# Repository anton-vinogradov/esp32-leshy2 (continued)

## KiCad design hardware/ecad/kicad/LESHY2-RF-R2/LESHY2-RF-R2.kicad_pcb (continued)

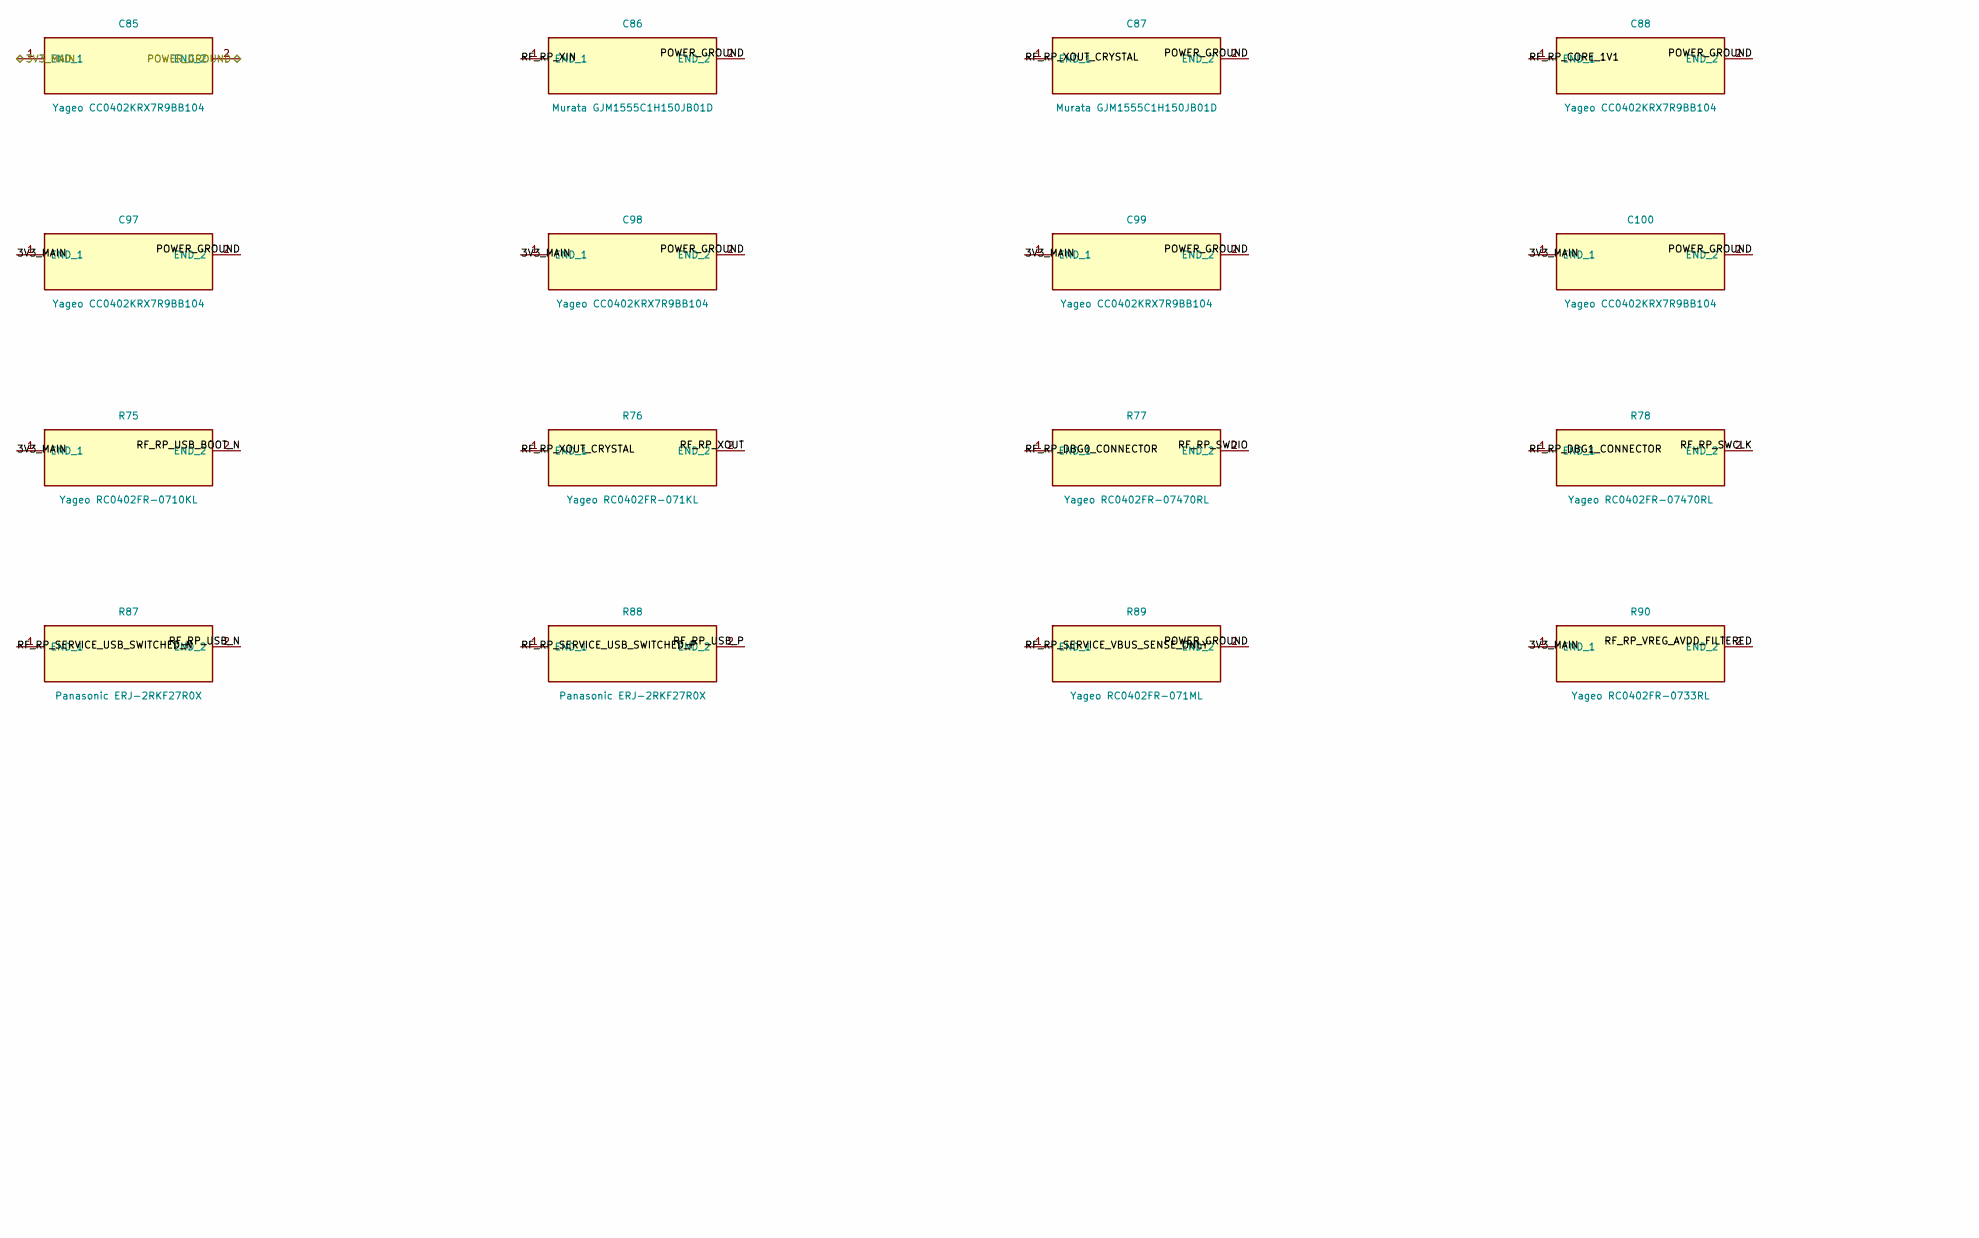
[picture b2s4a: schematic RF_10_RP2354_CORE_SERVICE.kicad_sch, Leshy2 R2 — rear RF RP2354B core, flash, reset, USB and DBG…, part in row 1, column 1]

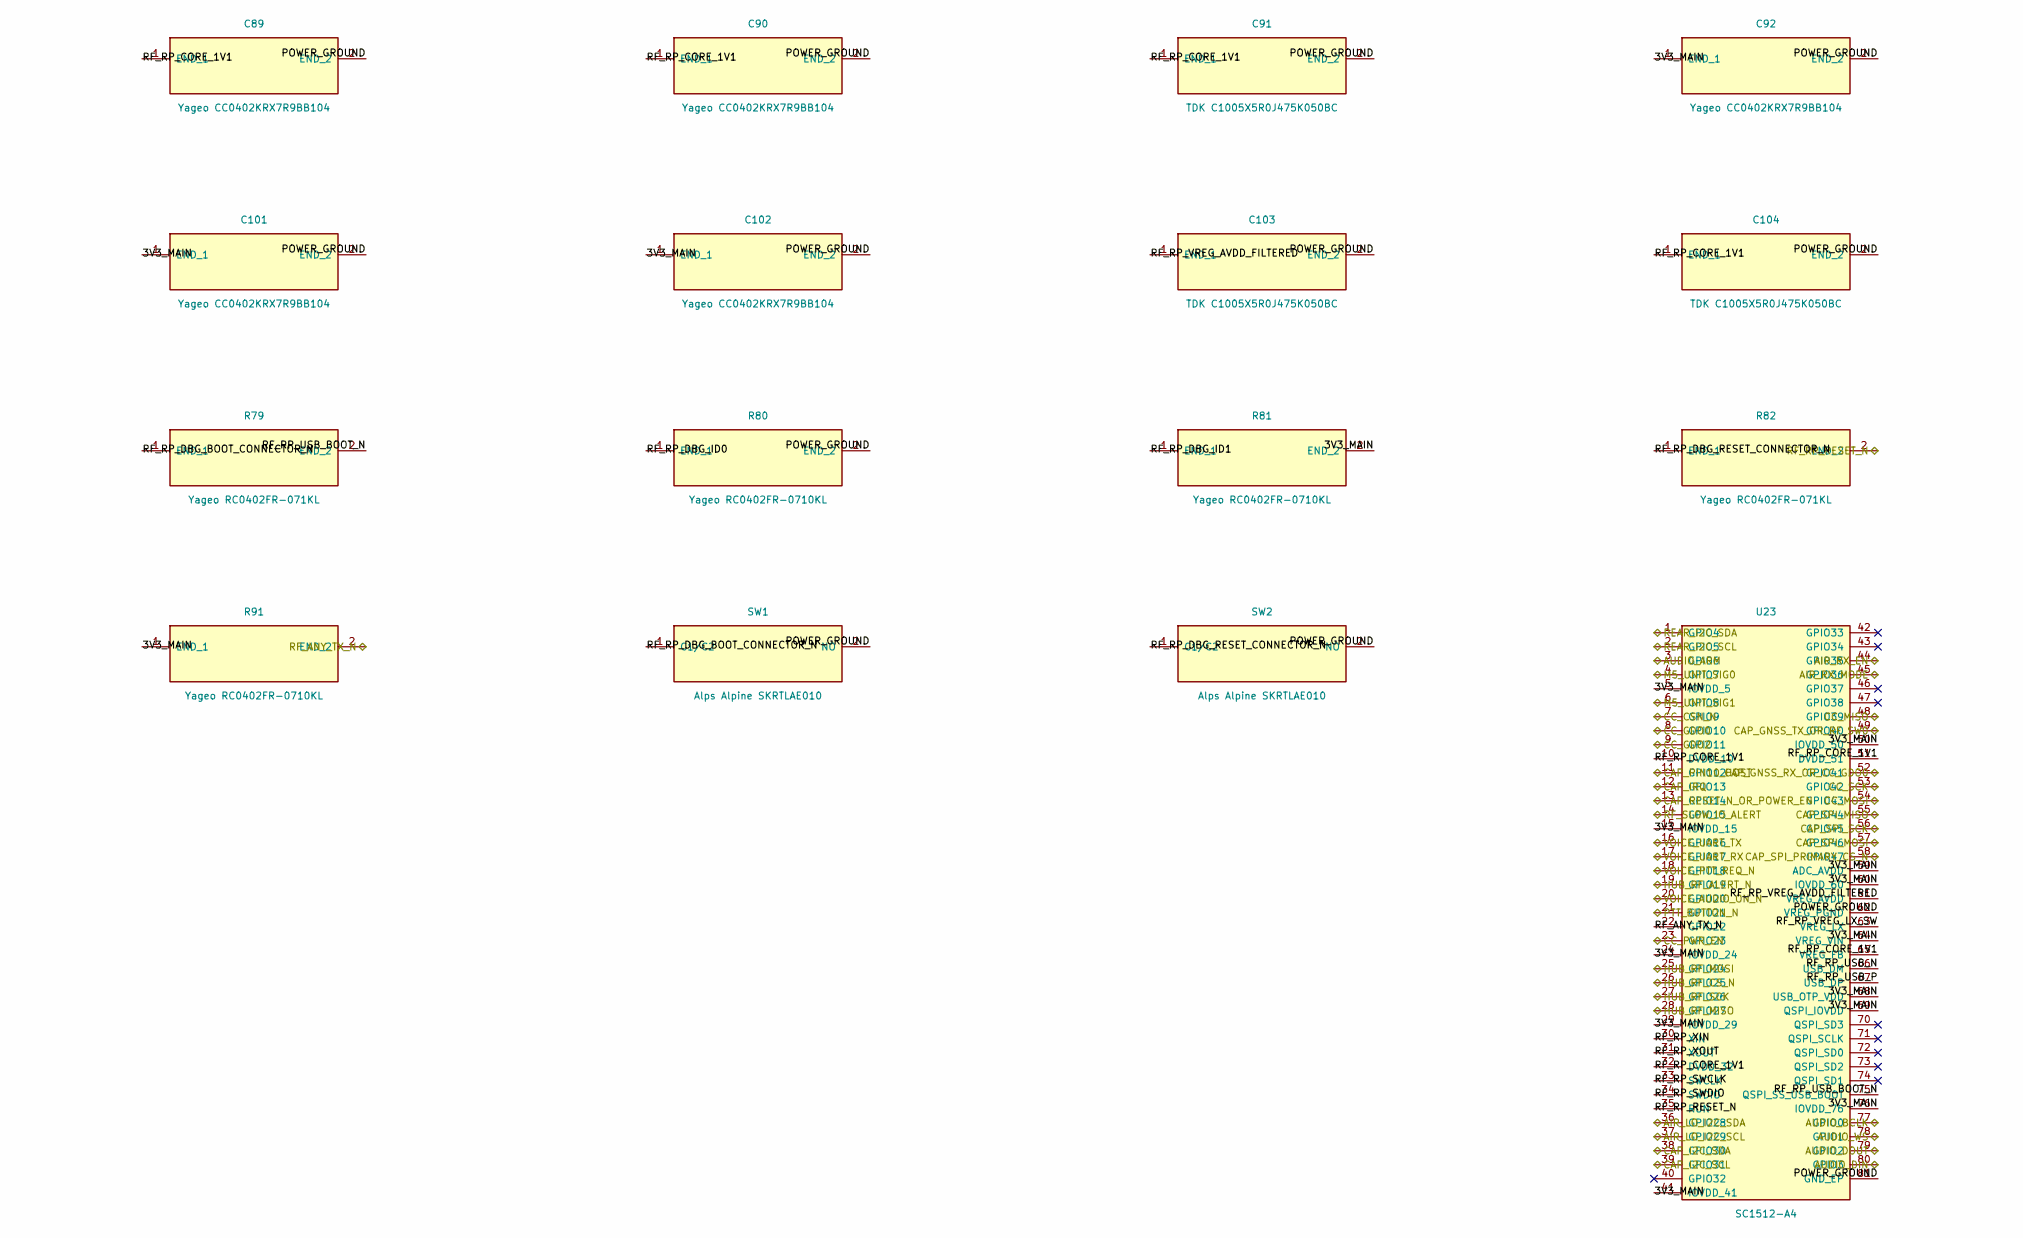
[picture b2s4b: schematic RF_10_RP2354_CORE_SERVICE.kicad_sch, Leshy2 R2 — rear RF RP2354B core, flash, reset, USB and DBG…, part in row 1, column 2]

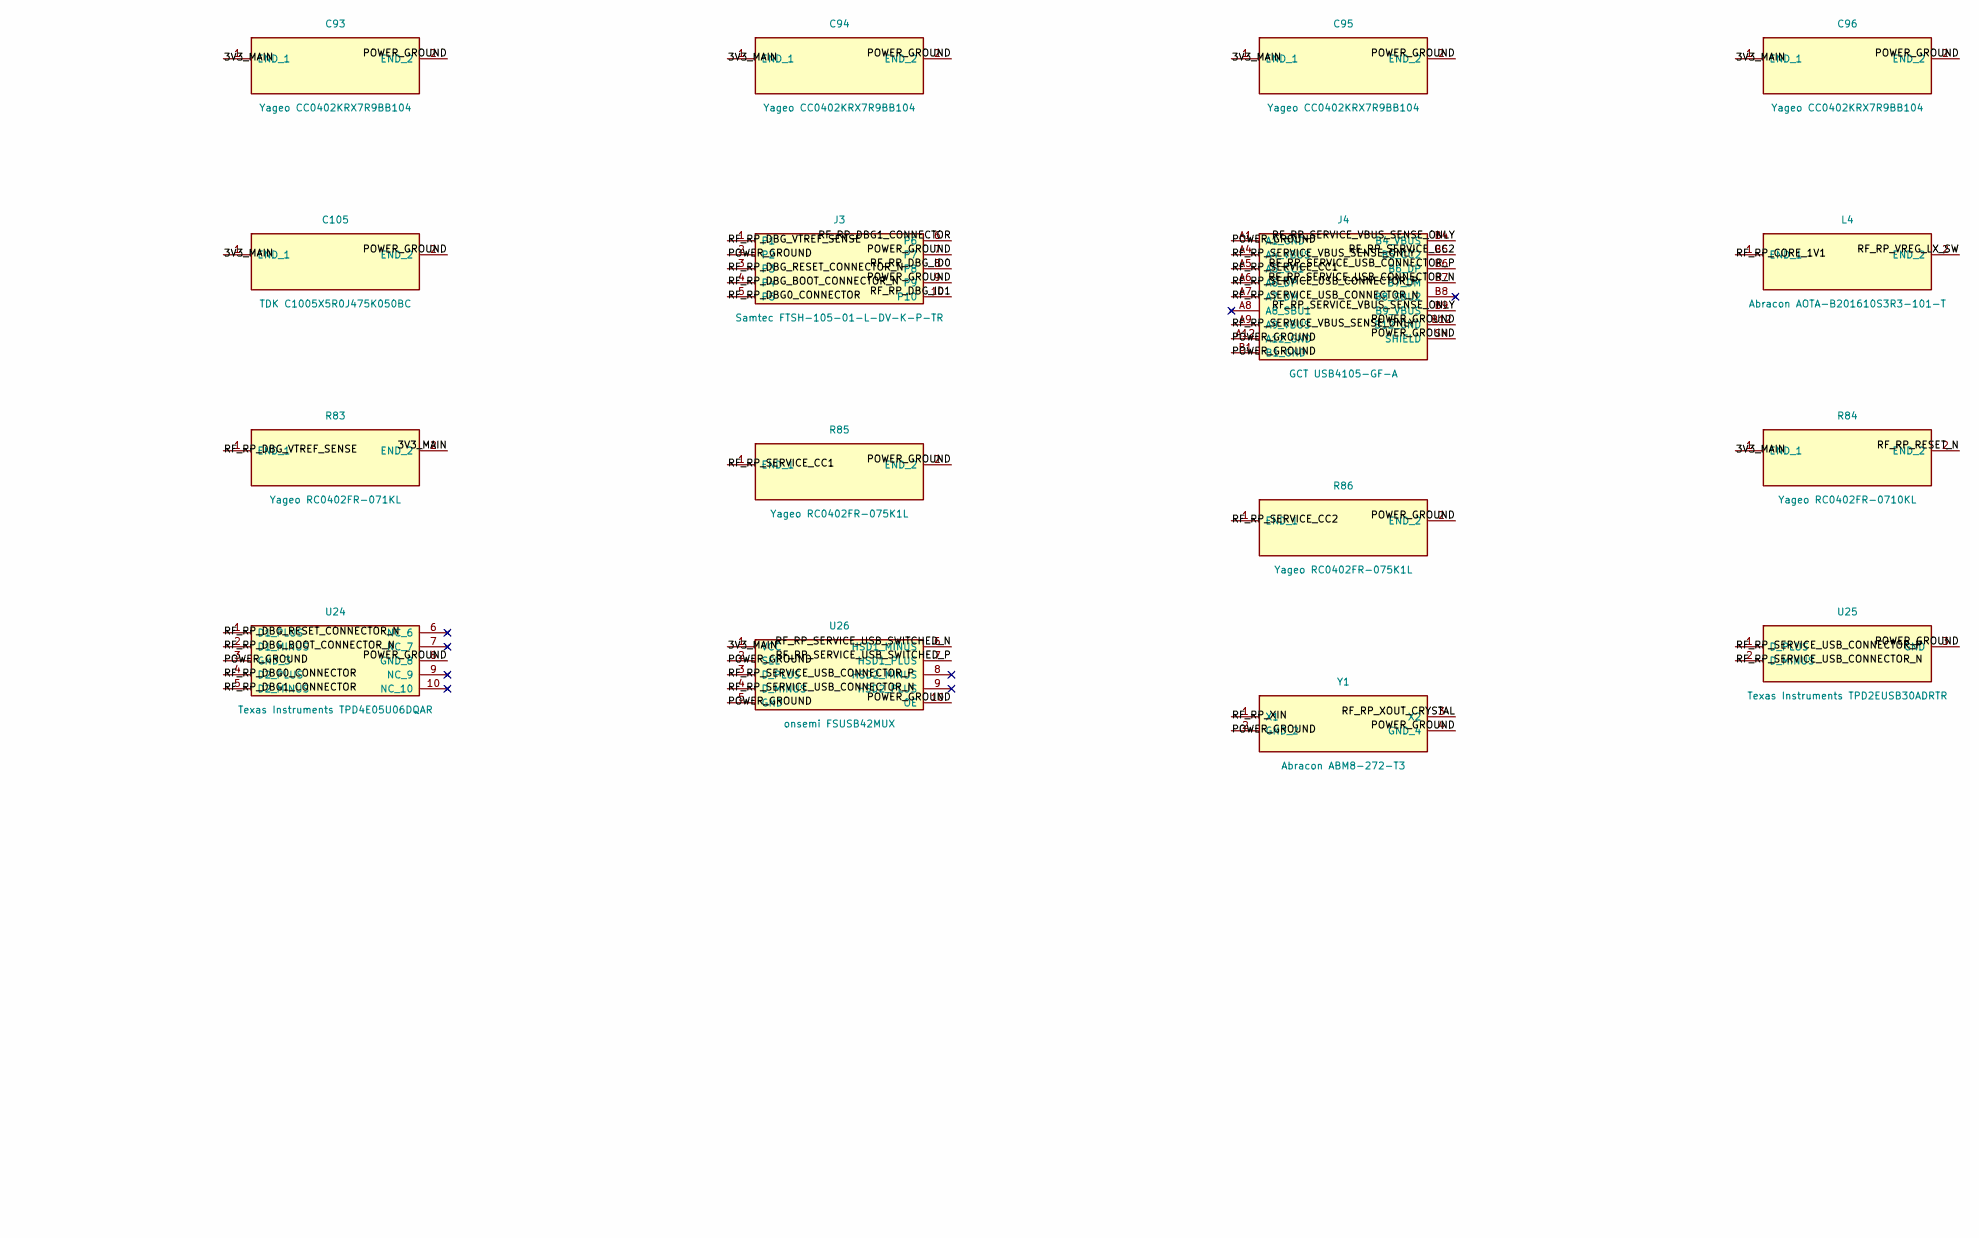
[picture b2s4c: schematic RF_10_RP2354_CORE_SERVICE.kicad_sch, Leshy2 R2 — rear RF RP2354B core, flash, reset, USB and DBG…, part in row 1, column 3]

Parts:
C85, C88, C89, C90, C92, C93, C94, C95, C96, C97, C98, C99, C100, C101, C102: Yageo CC0402KRX7R9BB104; C_0402_1005Metric
C86, C87: Murata GJM1555C1H150JB01D; C_0402_1005Metric
C91, C103, C104, C105: TDK C1005X5R0J475K050BC; C_0402_1005Metric
J3: Samtec FTSH-105-01-L-DV-K-P-TR; FTSH-105-01-L-DV-K-P-TR
J4: GCT USB4105-GF-A; USB_C_Receptacle_GCT_USB4105-xx-A_16P_TopMnt_Horizontal
L4: Abracon AOTA-B201610S3R3-101-T; L_Murata_DFE201610P
R75, R80, R81, R84, R91: Yageo RC0402FR-0710KL; R_0402_1005Metric
R76, R79, R82, R83: Yageo RC0402FR-071KL; R_0402_1005Metric
R77, R78: Yageo RC0402FR-07470RL; R_0402_1005Metric
R85, R86: Yageo RC0402FR-075K1L; R_0402_1005Metric
R87, R88: Panasonic ERJ-2RKF27R0X; R_0402_1005Metric
R89: Yageo RC0402FR-071ML; R_0402_1005Metric
R90: Yageo RC0402FR-0733RL; R_0402_1005Metric
SW1, SW2: Alps Alpine SKRTLAE010; SW_Push_1P1T-MP_NO_Horizontal_Alps_SKRTLAE010
U23: SC1512-A4; QFN-80-1EP_10x10mm_P0.4mm_EP3.4x3.4mm
U24: Texas Instruments TPD4E05U06DQAR; USON-10_2.5x1.0mm_P0.5mm
U25: Texas Instruments TPD2EUSB30ADRTR; Texas_DRT-3
U26: onsemi FSUSB42MUX; MSOP-10_3x3mm_P0.5mm
Y1: Abracon ABM8-272-T3; Crystal_SMD_Abracon_ABM8G-4Pin_3.2x2.5mm

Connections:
/RF_01_USB_PD_CHARGE/POWER_GROUND: C85.2 (END_2), C86.2 (END_2), C87.2 (END_2), C88.2 (END_2), C89.2 (END_2), C90.2 (END_2), C91.2 (END_2), C92.2 (END_2), C93.2 (END_2), C94.2 (END_2), C95.2 (END_2), C96.2 (END_2), C97.2 (END_2), C98.2 (END_2), C99.2 (END_2), C100.2 (END_2), C101.2 (END_2), C102.2 (END_2), C103.2 (END_2), C104.2 (END_2), C105.2 (END_2), J3.2, J3.7, J3.9, J4.A1 (A1_GND), J4.A12 (A12_GND), J4.B1 (B1_GND), J4.B12 (B12_GND), J4.SH (SHIELD), R80.2 (END_2), R85.2 (END_2), R86.2 (END_2), R89.2 (END_2), SW1.2 (NO), SW2.2 (NO), U23.62 (VREG_PGND), U23.81 (GND_EP), U24.3 (GND_3), U24.8 (GND_8), U25.3 (GND), U26.2 (SEL), U26.5 (GND), U26.10 (OE), Y1.2 (GND_2), Y1.4 (GND_4); also elsewhere on the board
/RF_02_PACK_SAFETY_AON/3V3_MAIN: C85.1 (END_1), C92.1 (END_1), C93.1 (END_1), C94.1 (END_1), C95.1 (END_1), C96.1 (END_1), C97.1 (END_1), C98.1 (END_1), C99.1 (END_1), C100.1 (END_1), C101.1 (END_1), C102.1 (END_1), C105.1 (END_1), R75.1 (END_1), R81.2 (END_2), R83.2 (END_2), R84.1 (END_1), R90.1 (END_1), R91.1 (END_1), U23.5 (IOVDD_5), U23.15 (IOVDD_15), U23.24 (IOVDD_24), U23.29 (IOVDD_29), U23.41 (IOVDD_41), U23.50 (IOVDD_50), U23.59 (ADC_AVDD), U23.60 (IOVDD_60), U23.64 (VREG_VIN), U23.68 (USB_OTP_VDD), U23.69 (QSPI_IOVDD), U23.76 (IOVDD_76), U26.1 (VCC); also elsewhere on the board
/RF_10_RP2354_CORE_SERVICE/AUDIO_BCLK: U23.77 (GPIO0); also elsewhere on the board
/RF_10_RP2354_CORE_SERVICE/AUDIO_DIN: U23.80 (GPIO3); also elsewhere on the board
/RF_10_RP2354_CORE_SERVICE/AUDIO_DOUT: U23.79 (GPIO2); also elsewhere on the board
/RF_10_RP2354_CORE_SERVICE/AUDIO_WS: U23.78 (GPIO1); also elsewhere on the board
/RF_10_RP2354_CORE_SERVICE/CAP_GNSS_RX_OR_CC_GDO0: U23.52 (GPIO41); also elsewhere on the board
/RF_10_RP2354_CORE_SERVICE/CAP_GNSS_TX_OR_RF_SW0: U23.49 (GPIO40); also elsewhere on the board
/RF_10_RP2354_CORE_SERVICE/CAP_IRQ: U23.12 (GPIO13); also elsewhere on the board
/RF_10_RP2354_CORE_SERVICE/CAP_PIN10_HOST: U23.11 (GPIO12); also elsewhere on the board
/RF_10_RP2354_CORE_SERVICE/CAP_RESET_N_OR_POWER_EN: U23.13 (GPIO14); also elsewhere on the board
/RF_10_RP2354_CORE_SERVICE/CAP_SPI_MISO: U23.55 (GPIO44); also elsewhere on the board
/RF_10_RP2354_CORE_SERVICE/CAP_SPI_MOSI: U23.57 (GPIO46); also elsewhere on the board
/RF_10_RP2354_CORE_SERVICE/CAP_SPI_PRIMARY_CS_N: U23.58 (GPIO47); also elsewhere on the board
/RF_10_RP2354_CORE_SERVICE/CAP_SPI_SCK: U23.56 (GPIO45); also elsewhere on the board
/RF_10_RP2354_CORE_SERVICE/CC_PWR_EN: U23.23 (GPIO23); also elsewhere on the board
/RF_10_RP2354_CORE_SERVICE/HUB_RF_ALERT_N: U23.19 (GPIO19); also elsewhere on the board
/RF_10_RP2354_CORE_SERVICE/HUB_RF_CS_N: U23.26 (GPIO25); also elsewhere on the board
/RF_10_RP2354_CORE_SERVICE/HUB_RF_MISO: U23.28 (GPIO27); also elsewhere on the board
/RF_10_RP2354_CORE_SERVICE/HUB_RF_MOSI: U23.25 (GPIO24); also elsewhere on the board
/RF_10_RP2354_CORE_SERVICE/HUB_RF_SCK: U23.27 (GPIO26); also elsewhere on the board
/RF_10_RP2354_CORE_SERVICE/M5_UNIT_SIG0: U23.4 (GPIO7); also elsewhere on the board
/RF_10_RP2354_CORE_SERVICE/M5_UNIT_SIG1: U23.6 (GPIO8); also elsewhere on the board
/RF_10_RP2354_CORE_SERVICE/PTT_BUTTON_N: U23.21 (GPIO21); also elsewhere on the board
/RF_10_RP2354_CORE_SERVICE/RF_ANY_TX_N: R91.2 (END_2), U23.22 (GPIO22); also elsewhere on the board
/RF_10_RP2354_CORE_SERVICE/RF_RP_CORE_1V1: C88.1 (END_1), C89.1 (END_1), C90.1 (END_1), C91.1 (END_1), C104.1 (END_1), L4.1 (END_1), U23.10 (DVDD_10), U23.32 (DVDD_32), U23.51 (DVDD_51), U23.65 (VREG_FB)
/RF_10_RP2354_CORE_SERVICE/RF_RP_DBG0_CONNECTOR: J3.5, R77.1 (END_1), U24.4 (D2_PLUS)
/RF_10_RP2354_CORE_SERVICE/RF_RP_DBG1_CONNECTOR: J3.6, R78.1 (END_1), U24.5 (D2_MINUS)
/RF_10_RP2354_CORE_SERVICE/RF_RP_DBG_BOOT_CONNECTOR_N: J3.4, R79.1 (END_1), SW1.1 (C1/C2), U24.2 (D1_MINUS)
/RF_10_RP2354_CORE_SERVICE/RF_RP_DBG_ID0: J3.8, R80.1 (END_1)
/RF_10_RP2354_CORE_SERVICE/RF_RP_DBG_ID1: J3.10, R81.1 (END_1)
/RF_10_RP2354_CORE_SERVICE/RF_RP_DBG_RESET_CONNECTOR_N: J3.3, R82.1 (END_1), SW2.1 (C1/C2), U24.1 (D1_PLUS)
/RF_10_RP2354_CORE_SERVICE/RF_RP_DBG_VTREF_SENSE: J3.1, R83.1 (END_1)
/RF_10_RP2354_CORE_SERVICE/RF_RP_RESET_N: R82.2 (END_2), R84.2 (END_2), U23.35 (RUN); also elsewhere on the board
/RF_10_RP2354_CORE_SERVICE/RF_RP_SERVICE_CC1: J4.A5 (A5_CC1), R85.1 (END_1)
/RF_10_RP2354_CORE_SERVICE/RF_RP_SERVICE_CC2: J4.B5 (B5_CC2), R86.1 (END_1)
/RF_10_RP2354_CORE_SERVICE/RF_RP_SERVICE_USB_CONNECTOR_N: J4.A7 (A7_DM), J4.B7 (B7_DM), U25.2 (D_MINUS), U26.4 (D_MINUS)
/RF_10_RP2354_CORE_SERVICE/RF_RP_SERVICE_USB_CONNECTOR_P: J4.A6 (A6_DP), J4.B6 (B6_DP), U25.1 (D_PLUS), U26.3 (D_PLUS)
/RF_10_RP2354_CORE_SERVICE/RF_RP_SERVICE_USB_SWITCHED_N: R87.1 (END_1), U26.6 (HSD1_MINUS)
/RF_10_RP2354_CORE_SERVICE/RF_RP_SERVICE_USB_SWITCHED_P: R88.1 (END_1), U26.7 (HSD1_PLUS)
/RF_10_RP2354_CORE_SERVICE/RF_RP_SERVICE_VBUS_SENSE_ONLY: J4.A4 (A4_VBUS), J4.A9 (A9_VBUS), J4.B4 (B4_VBUS), J4.B9 (B9_VBUS), R89.1 (END_1)
/RF_10_RP2354_CORE_SERVICE/RF_RP_SWCLK: R78.2 (END_2), U23.33 (SWCLK)
/RF_10_RP2354_CORE_SERVICE/RF_RP_SWDIO: R77.2 (END_2), U23.34 (SWDIO)
/RF_10_RP2354_CORE_SERVICE/RF_RP_USB_BOOT_N: R75.2 (END_2), R79.2 (END_2), U23.75 (QSPI_SS_USB_BOOT)
/RF_10_RP2354_CORE_SERVICE/RF_RP_USB_N: R87.2 (END_2), U23.66 (USB_DM)
/RF_10_RP2354_CORE_SERVICE/RF_RP_USB_P: R88.2 (END_2), U23.67 (USB_DP)
/RF_10_RP2354_CORE_SERVICE/RF_RP_VREG_AVDD_FILTERED: C103.1 (END_1), R90.2 (END_2), U23.61 (VREG_AVDD)
/RF_10_RP2354_CORE_SERVICE/RF_RP_VREG_LX_SW: L4.2 (END_2), U23.63 (VREG_LX)
/RF_10_RP2354_CORE_SERVICE/RF_RP_XIN: C86.1 (END_1), U23.30 (XIN), Y1.1 (X1)
/RF_10_RP2354_CORE_SERVICE/RF_RP_XOUT: R76.2 (END_2), U23.31 (XOUT)
/RF_10_RP2354_CORE_SERVICE/RF_RP_XOUT_CRYSTAL: C87.1 (END_1), R76.1 (END_1), Y1.3 (X2)
/RF_10_RP2354_CORE_SERVICE/RF_SLOW_IO_ALERT: U23.14 (GPIO15); also elsewhere on the board
/RF_10_RP2354_CORE_SERVICE/VOICE_PTT_REQ_N: U23.18 (GPIO18); also elsewhere on the board
/RF_10_RP2354_CORE_SERVICE/VOICE_UART_TX: U23.16 (GPIO16); also elsewhere on the board
/RF_20_CC1101_VOICE_TX/CC_CSN_N: U23.7 (GPIO9); also elsewhere on the board
/RF_20_CC1101_VOICE_TX/CC_GDO0: U23.8 (GPIO10); also elsewhere on the board
/RF_20_CC1101_VOICE_TX/CC_GDO2: U23.9 (GPIO11); also elsewhere on the board
/RF_20_CC1101_VOICE_TX/CC_MISO: U23.48 (GPIO39); also elsewhere on the board
/RF_20_CC1101_VOICE_TX/CC_MOSI: U23.54 (GPIO43); also elsewhere on the board
/RF_20_CC1101_VOICE_TX/CC_SCK: U23.53 (GPIO42); also elsewhere on the board
/RF_20_CC1101_VOICE_TX/VOICE_AUDIO_ON_N: U23.20 (GPIO20); also elsewhere on the board
/RF_20_CC1101_VOICE_TX/VOICE_UART_RX: U23.17 (GPIO17); also elsewhere on the board
/RF_21_BROADCAST_AIRBAND_RX/AIR_LO_I2C_SCL: U23.37 (GPIO29); also elsewhere on the board
/RF_21_BROADCAST_AIRBAND_RX/AIR_LO_I2C_SDA: U23.36 (GPIO28); also elsewhere on the board
/RF_21_BROADCAST_AIRBAND_RX/AIR_RX_EN: U23.44 (GPIO35); also elsewhere on the board
/RF_21_BROADCAST_AIRBAND_RX/AIR_RX_MODE: U23.45 (GPIO36); also elsewhere on the board
/RF_22_AUDIO_CODEC_IO/AUDIO_ARM: U23.3 (GPIO6); also elsewhere on the board
/RF_22_AUDIO_CODEC_IO/REAR_I2C_SCL: U23.2 (GPIO5); also elsewhere on the board
/RF_22_AUDIO_CODEC_IO/REAR_I2C_SDA: U23.1 (GPIO4); also elsewhere on the board
/RF_30_U214_U219_M5_EXT/CAP_I2C_SCL: U23.39 (GPIO31); also elsewhere on the board
/RF_30_U214_U219_M5_EXT/CAP_I2C_SDA: U23.38 (GPIO30); also elsewhere on the board
